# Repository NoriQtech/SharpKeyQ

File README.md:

## はじめに
このプロジェクトは、[engineers@work](https://eaw.app/) によって開発された SharpKey Multi HID Interface について、DIY用のPCB基板を設計し、動作/検証をする試みです。

海外のコアな8BitレトロPCファンが日本のユニークな8Bitパソコンを使いこなすために、日夜、解析・研究を行い、今も新しいプロダクトを生み出していることに敬意を表します。

## オリジナル
SharpKey Multi HID Interface のオリジナルプロジェクトについては、下記を参照してください。

* [engineers@work](https://eaw.app/)
* [SharpKey Multi-HID Interface](https://eaw.app/sharpkey/)
* [ユーザーマニュアル](https://eaw.app/sharpkey-usermanual/)
* [テクニカルガイド](https://eaw.app/sharpkey-technicalguide/)
* [GitHub](https://github.com/pdsmart)

## このプロジェクト
このプロジェクトはオリジナルコードからビルド可能な状態に修正を加えたものです。
機能は全てオリジナルに準じます。
また、回路図や基板デザインはDIY可能な設計に置き換えられています。

詳細は下記を参照してください。

[JunkQ yard SharpKeyQ](https://junkqyard.blogspot.com/p/sharpkeyq.html)

## アップデート
2024-02-09 MZ-5665モジュールの対応<br/>
2023-11-26 最初のコミット

## ライセンス
オリジナルライセンスに基づき、SharpKey Multi HID Interface の設計、ハードウェアおよびソフトウェアは、GNU Public License v3 に基づいてライセンスされています。

## The Gnu Public License v3
The source and binary files in this project marked as GPL v3 are free software: you can redistribute it and-or modify it under the terms of the GNU General Public License as published by the Free Software Foundation, either version 3 of the License, or (at your option) any later version.

The source files are distributed in the hope that it will be useful, but WITHOUT ANY WARRANTY; without even the implied warranty of MERCHANTABILITY or FITNESS FOR A PARTICULAR PURPOSE. See the GNU General Public License for more details.

You should have received a copy of the GNU General Public License along with this program. If not, see http://www.gnu.org/licenses/.

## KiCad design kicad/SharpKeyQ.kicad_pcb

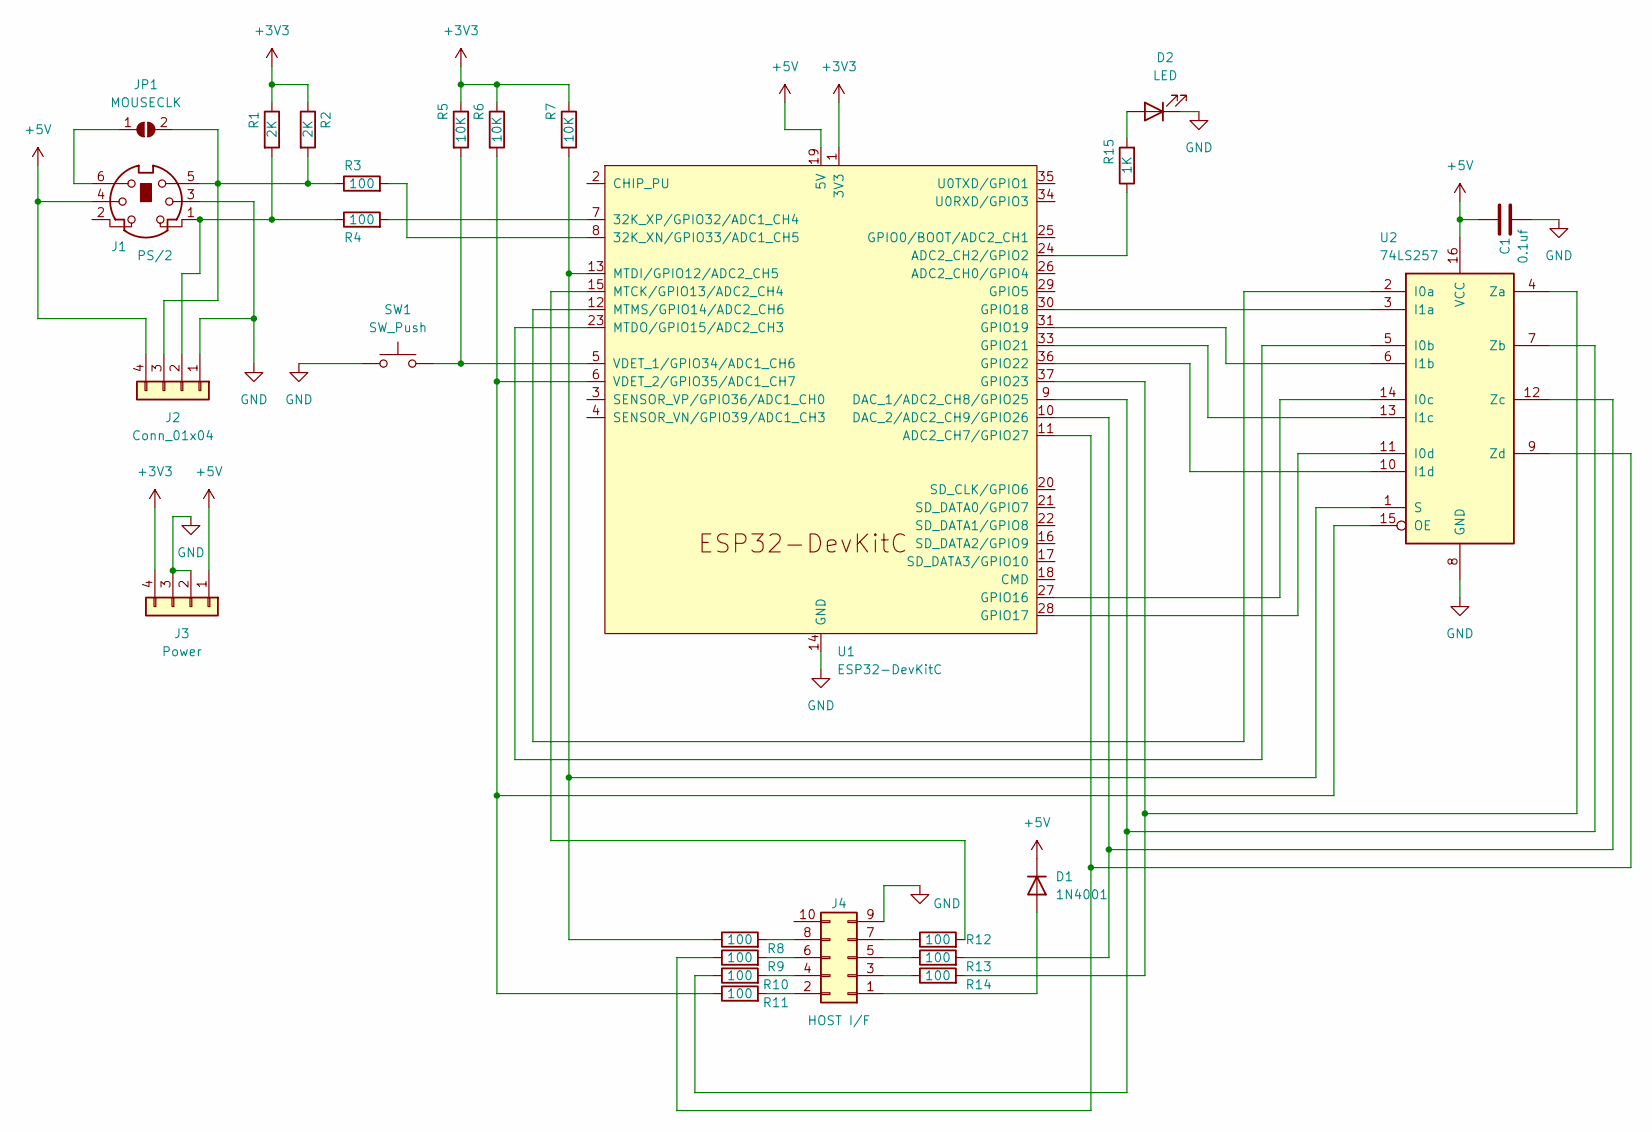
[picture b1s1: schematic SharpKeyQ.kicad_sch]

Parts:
C1: 0.1uf; C_Disc_D4.3mm_W1.9mm_P5.00mm
D1: 1N4001; D_DO-34_SOD68_P7.62mm_Horizontal
D2: LED; LED_D3.0mm
J1: PS/2; Connector_Mini-DIN_Female_6Pin_2rows
J2: Conn_01x04; PinHeader_1x04_P2.54mm_Vertical
J3: Power; PinHeader_1x04_P2.54mm_Vertical
J4: HOST I/F; PinHeader_2x05_P2.54mm_Horizontal
JP1: MOUSECLK; SolderJumper-2_P1.3mm_Open_RoundedPad1.0x1.5mm
R1, R2: 2K; R_Axial_DIN0204_L3.6mm_D1.6mm_P7.62mm_Horizontal
R3, R4, R8, R9, R10, R11, R12, R13, R14: 100; R_Axial_DIN0204_L3.6mm_D1.6mm_P7.62mm_Horizontal
R5, R6, R7: 10K; R_Axial_DIN0204_L3.6mm_D1.6mm_P7.62mm_Horizontal
R15: 1K; R_Axial_DIN0204_L3.6mm_D1.6mm_P7.62mm_Horizontal
SW1: SW_Push; SW_Tactile_SKHH_Angled
U1: ESP32-DevKitC
U2: 74LS257; DIP-16_W7.62mm_Socket

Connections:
+3V3: J3.4, R1.1, R2.1, R5.1, R6.1, R7.1, U1.1 (3V3)
+5V: C1.1, D1.1 (K), J1.4, J2.4, J3.1, U1.19 (5V), U2.16 (VCC)
GND: C1.2, D2.1 (K), J1.3, J2.1, J3.2, J3.3, J4.9, SW1.2, U1.14 (GND), U1.32 (GND), U1.38 (GND), U2.8 (GND)
unnamed: D1.2 (A), J4.1
unnamed: D2.2 (A), R15.2
unnamed: J1.1, J2.2, R1.2, R4.1
unnamed: J1.5, J2.3, JP1.2 (B), R2.2, R3.1
unnamed: J4.2, R11.2
unnamed: J4.3, R14.1
unnamed: J4.4, R10.2
unnamed: J4.5, R13.1
unnamed: J4.6, R9.2
unnamed: J4.7, R12.1
unnamed: J4.8, R8.2
unnamed: J1.6, JP1.1 (A)
unnamed: R3.2, U1.8 (32K_XN/GPIO33/ADC1_CH5)
unnamed: R4.2, U1.7 (32K_XP/GPIO32/ADC1_CH4)
unnamed: R15.1, U1.24 (ADC2_CH2/GPIO2)
unnamed: R9.1, U1.11 (ADC2_CH7/GPIO27), U2.9 (Zd)
unnamed: R10.1, U1.9 (DAC_1/ADC2_CH8/GPIO25), U2.7 (Zb)
unnamed: R13.2, U1.10 (DAC_2/ADC2_CH9/GPIO26), U2.12 (Zc)
unnamed: U1.27 (GPIO16), U2.14 (I0c)
unnamed: U1.28 (GPIO17), U2.11 (I0d)
unnamed: U1.30 (GPIO18), U2.3 (I1a)
unnamed: U1.31 (GPIO19), U2.6 (I1b)
unnamed: U1.33 (GPIO21), U2.13 (I1c)
unnamed: U1.36 (GPIO22), U2.10 (I1d)
unnamed: R14.2, U1.37 (GPIO23), U2.4 (Za)
unnamed: R12.2, U1.15 (MTCK/GPIO13/ADC2_CH4)
unnamed: R7.2, R8.1, U1.13 (MTDI/GPIO12/ADC2_CH5), U2.1 (S)
unnamed: U1.23 (MTDO/GPIO15/ADC2_CH3), U2.5 (I0b)
unnamed: U1.12 (MTMS/GPIO14/ADC2_CH6), U2.2 (I0a)
unnamed: R5.2, SW1.1, U1.5 (VDET_1/GPIO34/ADC1_CH6)
unnamed: R6.2, R11.1, U1.6 (VDET_2/GPIO35/ADC1_CH7), U2.15 (OE)

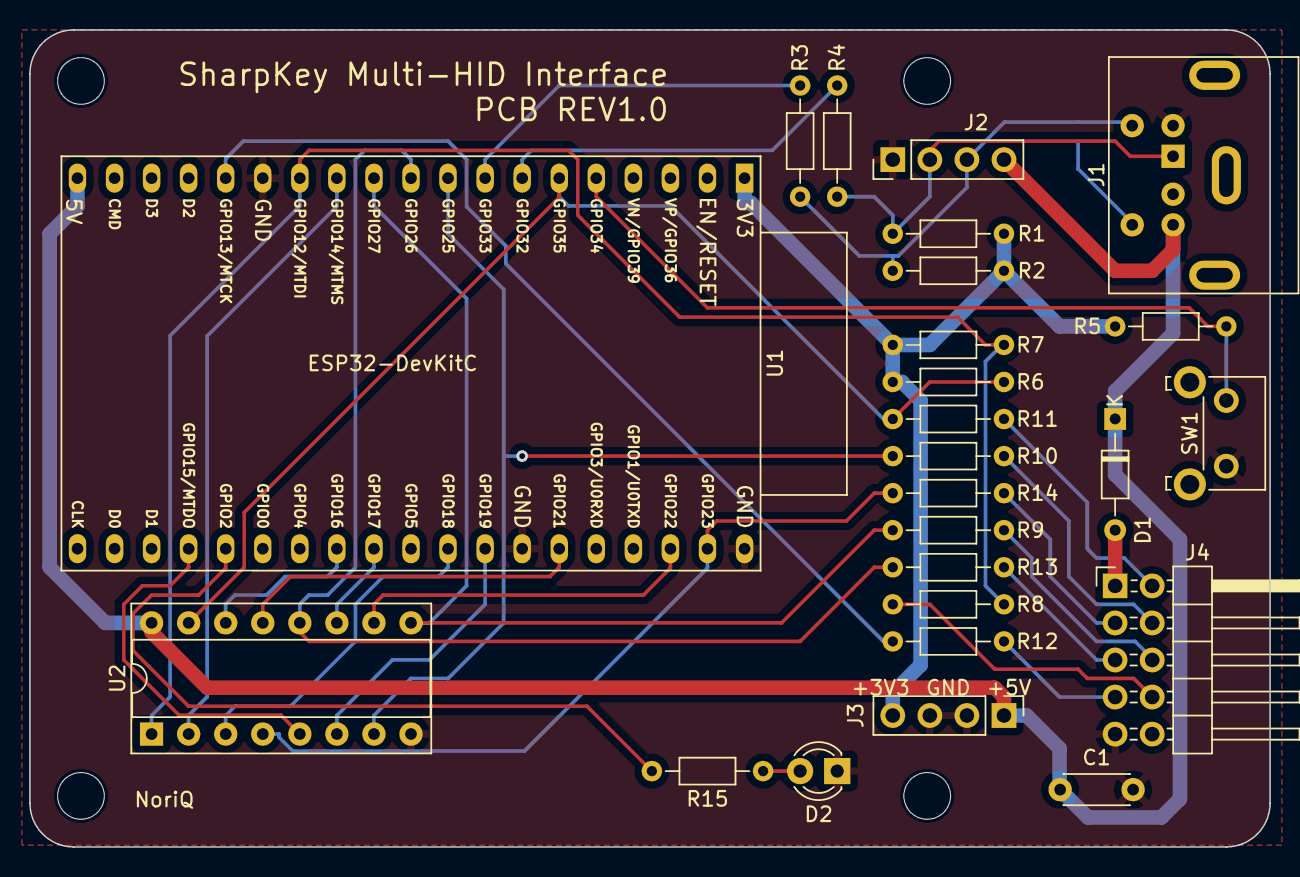
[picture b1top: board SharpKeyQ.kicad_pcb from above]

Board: 2 copper layers, 85.0 x 56.0 mm, 30 parts (1 on the bottom side), 34 nets.

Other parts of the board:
REF1, REF2, REF3, REF4: MountingHole_3.2mm_M3

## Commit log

2023-11-26 first add
2023-11-26 Typo
2023-11-27 add picture
2024-02-06 add submodule
2024-02-09 Supported MZ5665 module.
2024-02-09 add wait
